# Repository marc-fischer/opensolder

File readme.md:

# Marcs OpenSolder
Fully open source JBC T245-compatible soldering station and tool holder, forked from [howie-j's opensolder](https://github.com/howie-j/opensolder)

## Introduction
When looking to buy a genuine JBC station to replace my dated ERSA icon Pico I've came across howie-j's opensolder. That was already pretty close to my requirements, so i forked this repo. 

## Goals:
- _T12 clone_ form factor that does not take up valuable bench space
- Optional USB connection to PID tune and compensate offsets
- Add a tag-connect debug connector 
- Add a I2C to the breakout to be able to extend functionality afterwards (ie. desolder station)
- JBC T245 tip compatibility, with similar performance to the original station
- QoL features that the CDB station have, like auto standby, tip remover, holder, tip cleaner etc.
- Simple design using cheap off-the-shelf parts
- A compact handpiece stand with these features:
	- Detection when the handpiece is in the tool holder (auto standby)
	- Detection when you're about to swap tips (cut power)
	- Integrated tip remover, tip storage, tip cleaner and a soldering wire spool holder
	- Simple to build

## Design Specifications
- 24V toroidal transformer
- Zero Crossing AC switching
- OLED display and rotary encoder for adjusting temperature
- Compact and low profile design
- Super fast heatup time (~4s)
- Hardware should be mostly 3D printable, and easy to build using regular tools

## Station
  
The station is built in a Hammond enclosure, with a center mounted transformer. The PCB is mounted to the custom front panel, and all 230VAC connections is in the rear of the chassis.
There is two connectors on the rear panel, one for connecting to the stand, and an optional ST-link connector for firmware upgrades.

## Stand
  
The stand is made of 3D-printed parts, a genuine JBC tool holder, a tip remover made from aluminium angle and some fasteners. Most parts can be made from aluminium sheet if that is preferred.

## Schematic
This is the internal connections of the JBC C245 cartridge:  

[__The schematic__](https://github.com/howie-j/OpenSolder/raw/main/hardware/schematic.pdf) is divided into three sheets: AC, Analog and MCU.

### AC
The 24VAC input is fused, then connected directly to the tip center pin (5). Switching is done with two N-channel mosfets, driven by a Si8751 isolated gate driver.

Zero cross detection is done with an AC optocoupler, and the current is limited by three 10k resistors (to reduce BOM items). This solution triggers the ZeroCross about 90uS prematurely, and that is compensated for in firmware.

The MCU and thermocouple frontend must be electrically isolated, and a 24V to 5V DCDC PSU module solves that problem. The DCDC-supply is preregulated with a 24V linear regulator, and post-regulated to 3.3V with a LDO. This power supply chain is in need of some simplification, but the components are few and cheap, and it works great for now.

### Analog
The thermocouple signal is amplified with a MAX4238 chopper opamp, with a fairly arbitrary amplification of 221, since temperature calibration is done in firmware anyway. No negative supply rail means the thermocouple can't sense lower temperatures than room temp, but that's not needed for a soldering station.

Long handpiece wires means lots of crosstalk, so a pair of diodes clamps the thermocouple input at Vf. The MCU pin _TIP_CLAMP_ is driven low when power is applied to the handpiece, to clamp noise on the opamp input. When its time to measure tip temperature, the pin is set to input, and a delay waits for the RC filter to stabilize.

To sense if there is a tip cartridge in the handpiece, _TIP_CHECK_ is driven high. The low impedance of the thermocouple + heater (a few Ω's) will create a very low voltage drop. If the tip is removed, the Vf of the input protection diode will drive _THERMOCOUPLE_ADC_ close to 3.3V.

### MCU
A STM32F072 is used since I have a few of them in stock, but almost any STM32 could be adapted to work. To sense PCB temperature (and for cold junction compensation), an I2C temp sensor is added. The MCU might have an internal temperature sensor, but  have not looked into that yet.

The rotary encoder and handpiece stand inputs are filtered using plain RC filters. This, combined with the input hysteresis, removes most input noise. The TIM encoder inputs also have additional filtering and FSM redundancy.

## PCB
[___Check out this interactive BOM___](http://htmlpreview.github.io/?https://github.com/howie-j/OpenSolder/blob/main/hardware/bom/interactive_bom.html)

The PCB is quite low density, uses 0603 SMD components and is fully hand solderable with a microscope. Connections to the rear connectors (stand and I2C-2 breakout) is done via a 6-pin IDC connector, so no crimping of tiny connector pins are necessary. The PCB is mounted to the front panel via the rotary encoder and the handpiece connector.

## Firmware
The firmware is simple and functional, and uses a modified hysteresis temperature controller that is very fast but has some initial overshoot. Currently all default values are set in _opensolder.h_, and are reset when the station is powered off.

### TODO
Nothing is currently missing for regular functionality. However some features would be cool to have:

- More accurate temp control (PID or other controller)
- User changeable default values
- Menu for changing default values
- Better looking UI

## Links and Sources
[The unisolder project](https://github.com/sparkybg/UniSolder-5.2) 
[Marco Reps](https://youtu.be/GYIiOkr6x9o) 
[foldvarid93's JBC Soldering Station](https://github.com/foldvarid93/JBC_SolderingStation) 
[johnmx's eevblog thread](https://eevblog.com/forum/testgear/jbc-soldering-station-cd-2bc-complete-schematic-analysis/) 
[howie-j's opensolder](https://github.com/howie-j/opensolder)

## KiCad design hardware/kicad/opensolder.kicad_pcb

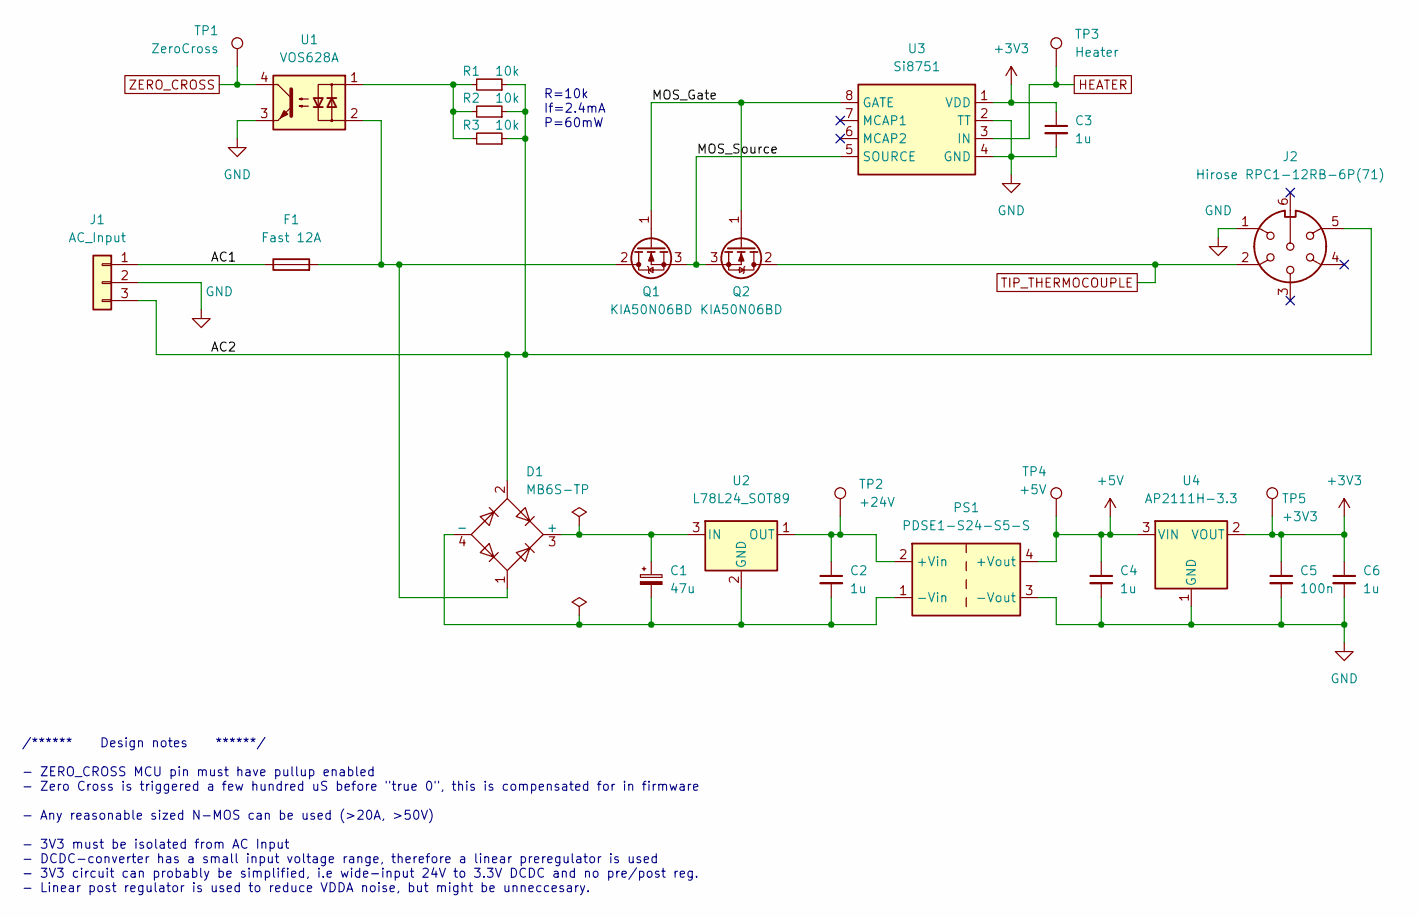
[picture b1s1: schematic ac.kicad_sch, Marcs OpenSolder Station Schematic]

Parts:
C1: 47u; CP_Radial_D8.0mm_P3.50mm
C2, C3, C4, C6: 1u; C_1210_3225Metric
C5: 100n; C_0805_2012Metric
D1: MB6S-TP; TO-269AA
F1: Fast 12A; Fuseholder_Cylinder-5x20mm_Schurter_0031_8201_Horizontal_Op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
J1: AC_Input; PhoenixContact_MSTBVA_2,5_3-G_1x03_P5.00mm_Vertical
J2: Hirose RPC1-12RB-6P(71); Hirose_RPC1
PS1: PDSE1-S24-S5-S; PDSE1_DCDC
Q1, Q2: KIA50N06BD; TO-252-2
R1, R2, R3: 10k; R_0603_1608Metric
TP1: ZeroCross; TestPoint_Pad_D1.0mm
TP2: +24V; TestPoint_Pad_D1.0mm
TP3: Heater; TestPoint_Pad_D1.0mm
TP4: +5V; TestPoint_Pad_D1.0mm
TP5: +3V3; TestPoint_Pad_D1.0mm
U1: VOS628A; SOP-4_4.4x2.6mm_P1.27mm
U2: L78L24_SOT89; SOT-89-3
U3: Si8751; SOIC-8_3.9x4.9mm_P1.27mm
U4: AP2111H-3.3; SOT-223

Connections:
+3V3: C3.1, C5.1, C6.1, TP5.1, U3.1 (VDD), U4.2 (VOUT); also elsewhere on the board
+5V: C4.1, PS1.4 (+Vout), TP4.1, U4.3 (VIN); also elsewhere on the board
/AC/AC1: F1.1, J1.1
/AC/AC2: D1.2, J1.3, J2.5, R1.1, R2.1, R3.1
/AC/MOS_Gate: Q1.1 (G), Q2.1 (G), U3.8 (GATE)
/AC/MOS_Source: Q1.3 (S), Q2.3 (S), U3.5 (SOURCE)
GND: C3.2, C4.2, C5.2, C6.2, J1.2, J2.1, PS1.3 (-Vout), U1.3, U3.2 (TT), U3.4 (GND), U4.1 (GND); also elsewhere on the board
HEATER: TP3.1, U3.3 (IN); also elsewhere on the board
unnamed: C1.1, D1.3 (+), U2.3 (IN)
unnamed: C1.2, C2.2, D1.4 (-), PS1.1 (-Vin), U2.2 (GND)
unnamed: C2.1, PS1.2 (+Vin), TP2.1, U2.1 (OUT)
unnamed: D1.1, F1.2, Q1.2 (D), U1.2
unnamed: R1.2, R2.2, R3.2, U1.1
TIP_THERMOCOUPLE: J2.2, Q2.2 (D); also elsewhere on the board
ZERO_CROSS: TP1.1, U1.4; also elsewhere on the board

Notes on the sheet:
R=10k If=2.4mA P=60mW
/****** Design notes ******/ - ZERO_CROSS MCU pin must have pullup enabled - Zero Cross is triggered a few hundred uS before "true 0", this is compensated for in firmware - Any reasonable sized N-MOS can be used (>20A, >50V) - 3V3 must be isolated from AC Input - DCDC-converter has a small input vo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

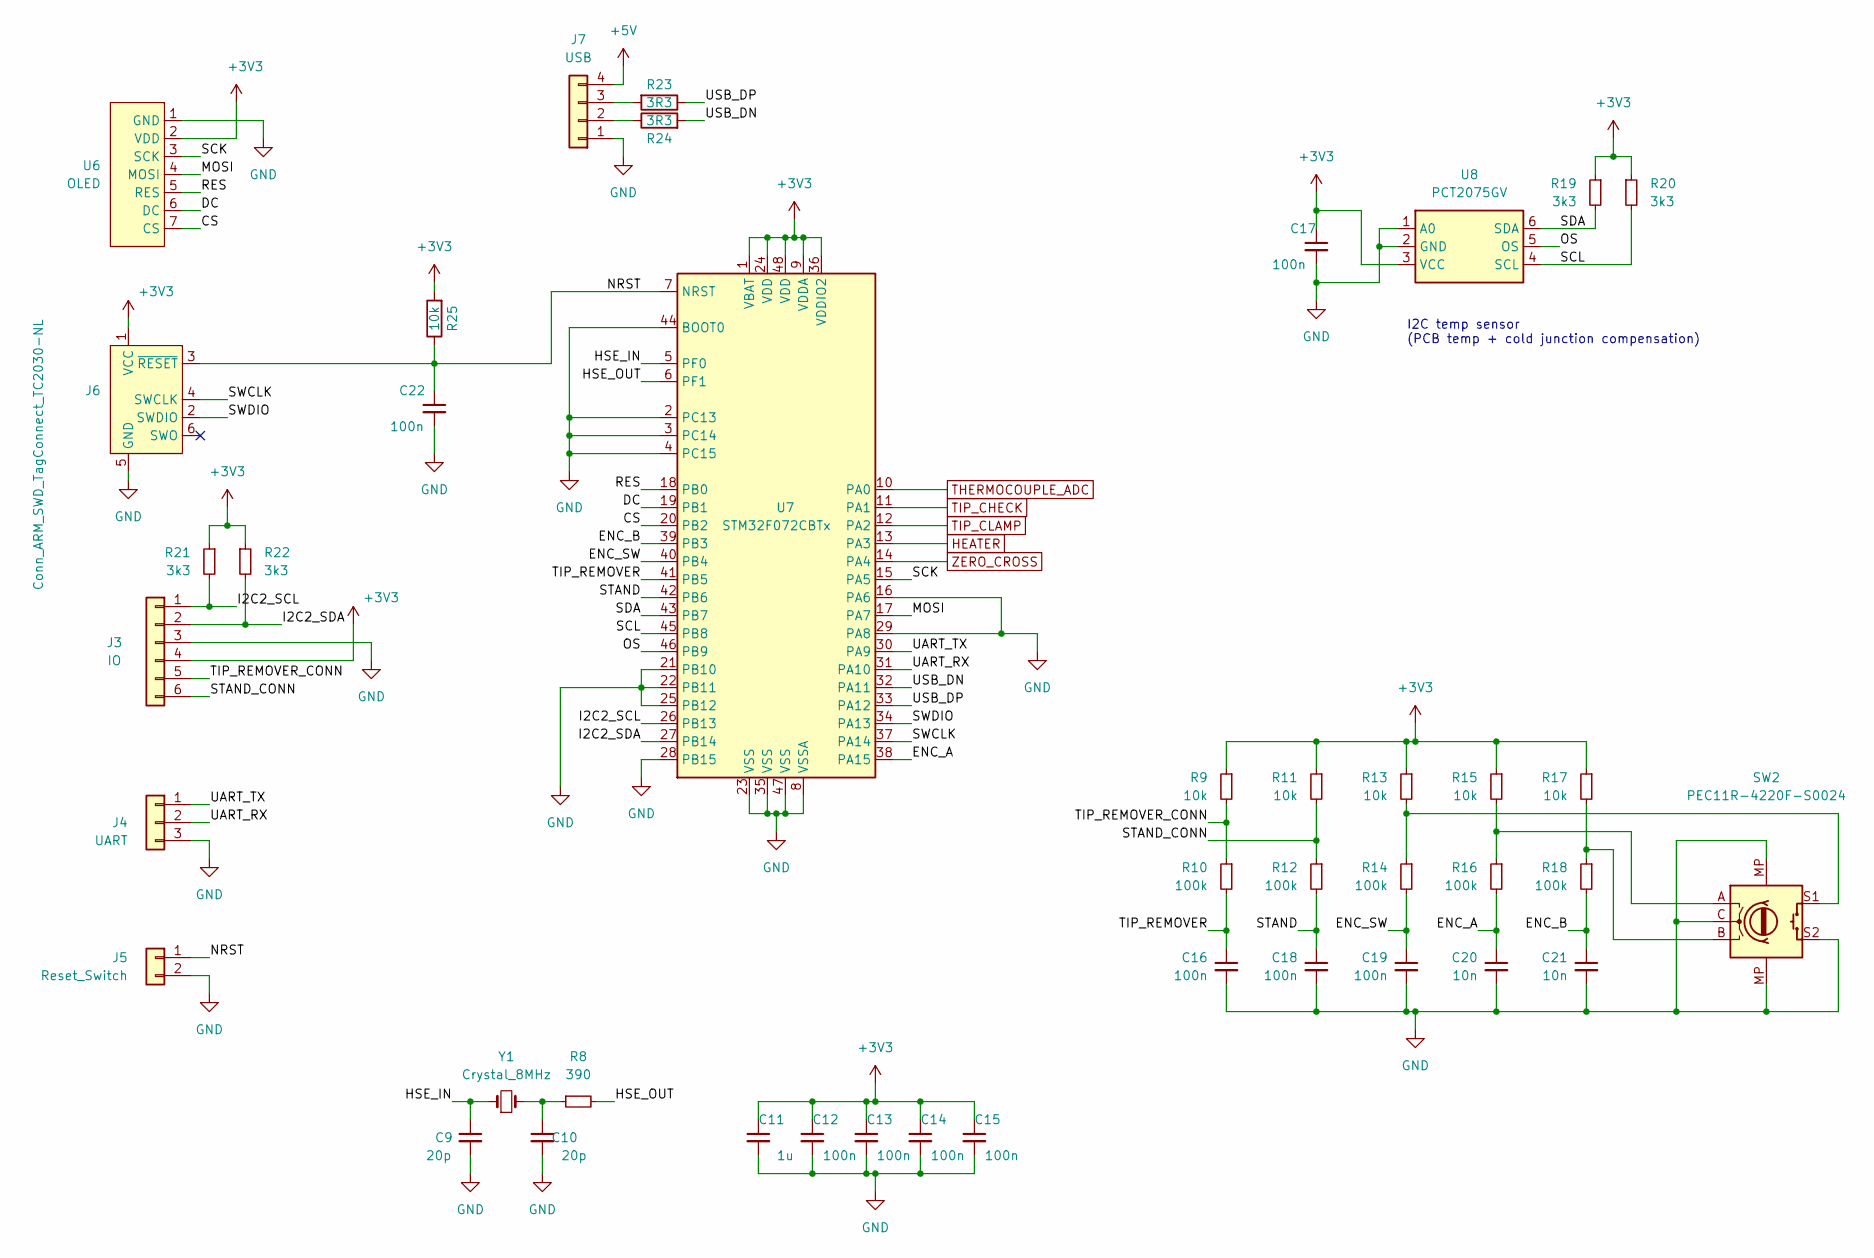
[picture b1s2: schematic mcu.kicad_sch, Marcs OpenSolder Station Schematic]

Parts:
C9, C10: 20p; C_0603_1608Metric
C11: 1u; C_1210_3225Metric
C12, C13, C14, C15: 100n; C_0805_2012Metric
C16, C17, C18, C19, C22: 100n; C_0603_1608Metric
C20, C21: 10n; C_0603_1608Metric
J3: IO; PinHeader_2x03_P2.54mm_Vertical
J4: UART; PinSocket_1x03_P2.54mm_Vertical
J5: Reset_Switch; PinSocket_1x02_P2.54mm_Vertical
J6: Conn_ARM_SWD_TagConnect_TC2030-NL; Tag-Connect_TC2030-IDC-NL_2x03_P1.27mm_Vertical
J7: USB; PinSocket_1x04_P2.54mm_Vertical
R8: 390; R_0603_1608Metric
R9, R11, R13, R15, R17, R25: 10k; R_0603_1608Metric
R10, R12, R14, R16, R18: 100k; R_0603_1608Metric
R19, R20, R21, R22: 3k3; R_0603_1608Metric
R23, R24: 3R3; R_0603_1608Metric
SW2: PEC11R-4220F-S0024; RotaryEncoder_PEC11R_PEC12R
U6: OLED; OLED_SSD1306_SPI_1.54
U7: STM32F072CBTx; LQFP-48_7x7mm_P0.5mm
U8: PCT2075GV; TSOP-6_1.65x3.05mm_P0.95mm
Y1: Crystal_8MHz; Crystal_SMD_HC49-SD

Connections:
+3V3: C11.1, C12.1, C13.1, C14.1, C15.1, C17.1, J3.4, J6.1 (VCC), R9.1, R11.1, R13.1, R15.1, R17.1, R19.1, R20.1, R21.1, R22.1, R25.2, U6.2 (VDD), U7.1 (VBAT), U7.9 (VDDA), U7.24 (VDD), U7.36 (VDDIO2), U7.48 (VDD), U8.3 (VCC); also elsewhere on the board
+5V: J7.4; also elsewhere on the board
/MCU/CS: U6.7 (CS), U7.20 (PB2)
/MCU/DC: U6.6 (DC), U7.19 (PB1)
/MCU/ENC_A: C20.1, R16.2, U7.38 (PA15)
/MCU/ENC_B: C21.1, R18.2, U7.39 (PB3)
/MCU/ENC_SW: C19.1, R14.2, U7.40 (PB4)
/MCU/HSE_IN: C9.1, U7.5 (PF0), Y1.1
/MCU/HSE_OUT: R8.2, U7.6 (PF1)
/MCU/I2C2_SCL: J3.1, R21.2, U7.26 (PB13)
/MCU/I2C2_SDA: J3.2, R22.2, U7.27 (PB14)
/MCU/MOSI: U6.4 (MOSI), U7.17 (PA7)
/MCU/NRST: C22.1, J5.1, J6.3 (~RESET), R25.1, U7.7 (NRST)
/MCU/OS: U7.46 (PB9), U8.5 (OS)
/MCU/RES: U6.5 (RES), U7.18 (PB0)
/MCU/SCK: U6.3 (SCK), U7.15 (PA5)
/MCU/SCL: R20.2, U7.45 (PB8), U8.4 (SCL)
/MCU/SDA: R19.2, U7.43 (PB7), U8.6 (SDA)
/MCU/STAND: C18.1, R12.2, U7.42 (PB6)
/MCU/STAND_CONN: J3.6, R11.2, R12.1
/MCU/SWCLK: J6.4 (SWCLK), U7.37 (PA14)
/MCU/SWDIO: J6.2 (SWDIO), U7.34 (PA13)
/MCU/TIP_REMOVER: C16.1, R10.2, U7.41 (PB5)
/MCU/TIP_REMOVER_CONN: J3.5, R9.2, R10.1
/MCU/UART_RX: J4.2, U7.31 (PA10)
/MCU/UART_TX: J4.1, U7.30 (PA9)
/MCU/USB_DN: R24.2, U7.32 (PA11)
/MCU/USB_DP: R23.1, U7.33 (PA12)
GND: C9.2, C10.2, C11.2, C12.2, C13.2, C14.2, C15.2, C16.2, C17.2, C18.2, C19.2, C20.2, C21.2, C22.2, J3.3, J4.3, J5.2, J6.5 (GND), J7.1, SW2.C, SW2.MP, SW2.S2, U6.1 (GND), U7.2 (PC13), U7.3 (PC14), U7.4 (PC15), U7.8 (VSSA), U7.16 (PA6), U7.21 (PB10), U7.22 (PB11), U7.23 (VSS), U7.25 (PB12), U7.28 (PB15), U7.29 (PA8), U7.35 (VSS), U7.44 (BOOT0), U7.47 (VSS), U8.1 (A0), U8.2 (GND); also elsewhere on the board
HEATER: U7.13 (PA3); also elsewhere on the board
unnamed: C10.1, R8.1, Y1.2
unnamed: J7.2, R24.1
unnamed: J7.3, R23.2
unnamed: R13.2, R14.1, SW2.S1
unnamed: R15.2, R16.1, SW2.A
unnamed: R17.2, R18.1, SW2.B
THERMOCOUPLE_ADC: U7.10 (PA0); also elsewhere on the board
TIP_CHECK: U7.11 (PA1); also elsewhere on the board
TIP_CLAMP: U7.12 (PA2); also elsewhere on the board
ZERO_CROSS: U7.14 (PA4); also elsewhere on the board

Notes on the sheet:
I2C temp sensor (PCB temp + cold junction compensation)

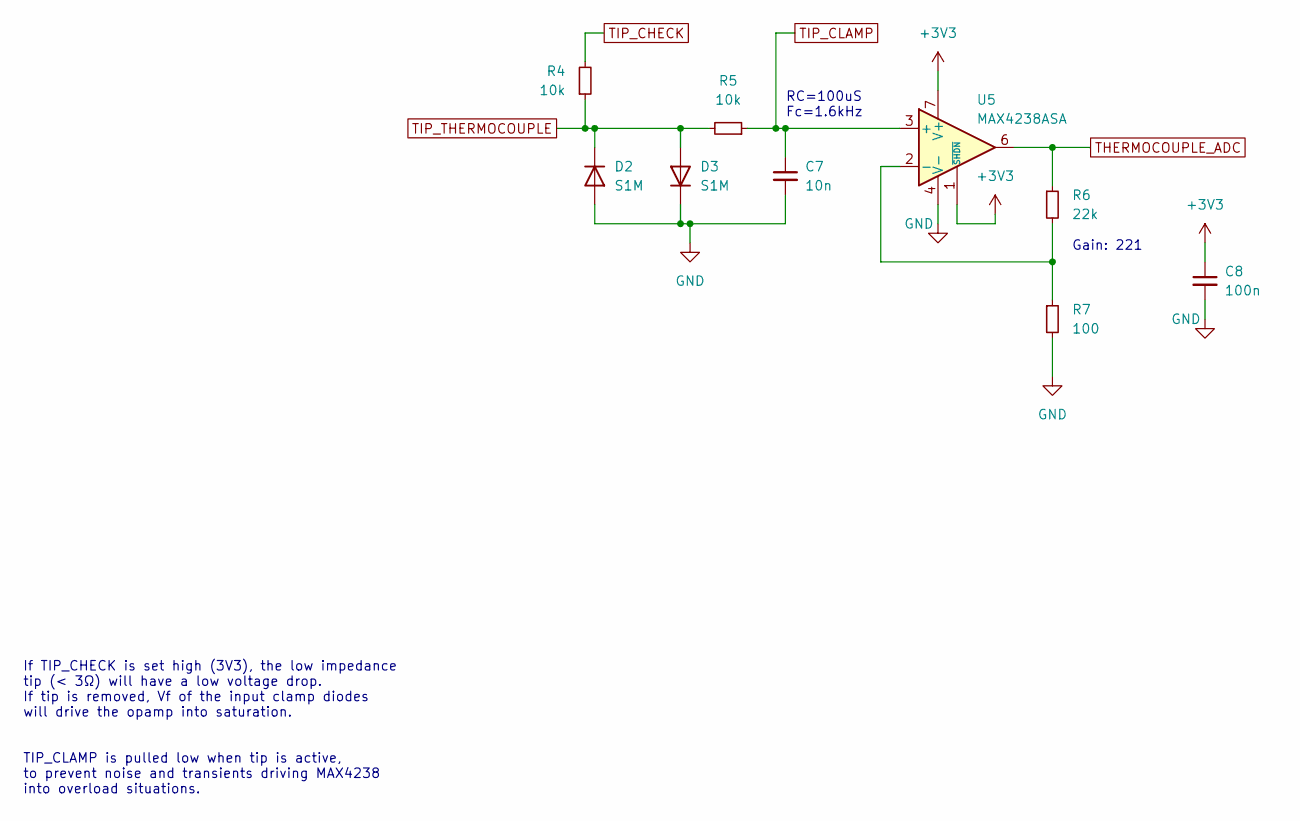
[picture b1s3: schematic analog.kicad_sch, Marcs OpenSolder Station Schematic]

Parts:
C7: 10n; C_0603_1608Metric
C8: 100n; C_0603_1608Metric
D2, D3: S1M; D_SMA
R4, R5: 10k; R_0603_1608Metric
R6: 22k; R_0603_1608Metric
R7: 100; R_0603_1608Metric
U5: MAX4238ASA; SOIC-8_3.9x4.9mm_P1.27mm

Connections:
+3V3: C8.1, U5.1 (~SHDN), U5.7 (V+); also elsewhere on the board
GND: C7.2, C8.2, D2.2 (A), D3.1 (K), R7.2, U5.4 (V-); also elsewhere on the board
unnamed: R6.2, R7.1, U5.2 (-)
THERMOCOUPLE_ADC: R6.1, U5.6; also elsewhere on the board
TIP_CHECK: R4.2; also elsewhere on the board
TIP_CLAMP: C7.1, R5.1, U5.3 (+); also elsewhere on the board
TIP_THERMOCOUPLE: D2.1 (K), D3.2 (A), R4.1, R5.2; also elsewhere on the board

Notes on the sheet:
Gain: 221
RC=100uS Fc=1.6kHz
If TIP_CHECK is set high (3V3), the low impedance tip (< 3Ω) will have a low voltage drop. If tip is removed, Vf of the input clamp diodes will drive the opamp into saturation. TIP_CLAMP is pulled low when tip is active, to prevent noise and transients driving MAX4238 into overload situations.

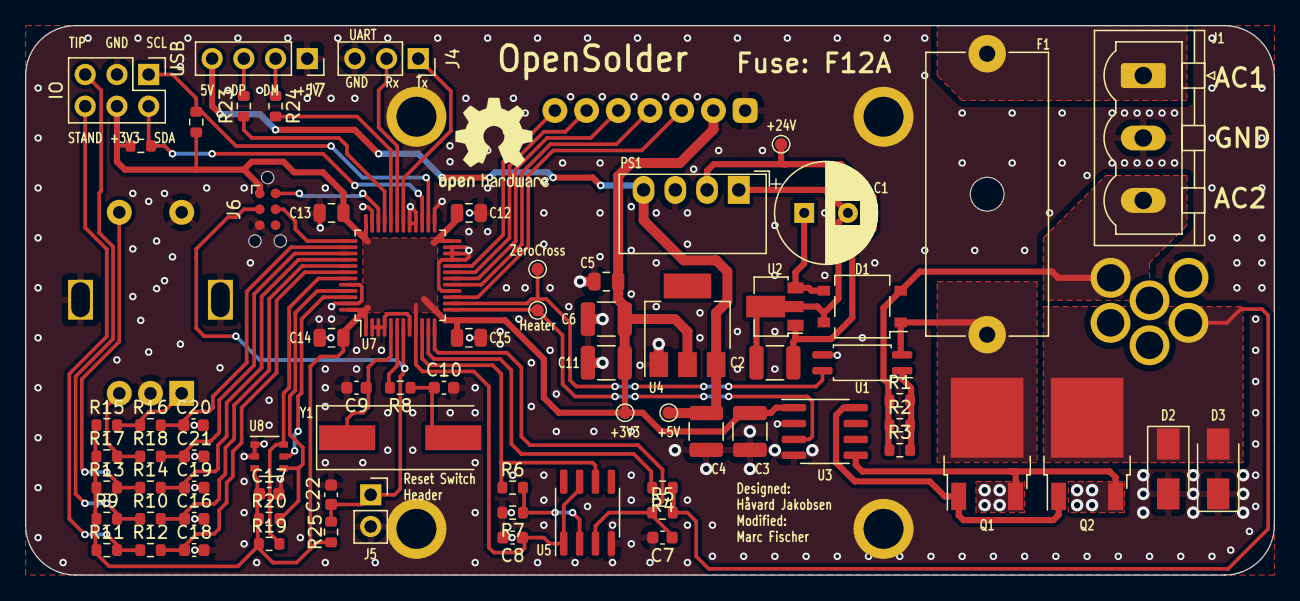
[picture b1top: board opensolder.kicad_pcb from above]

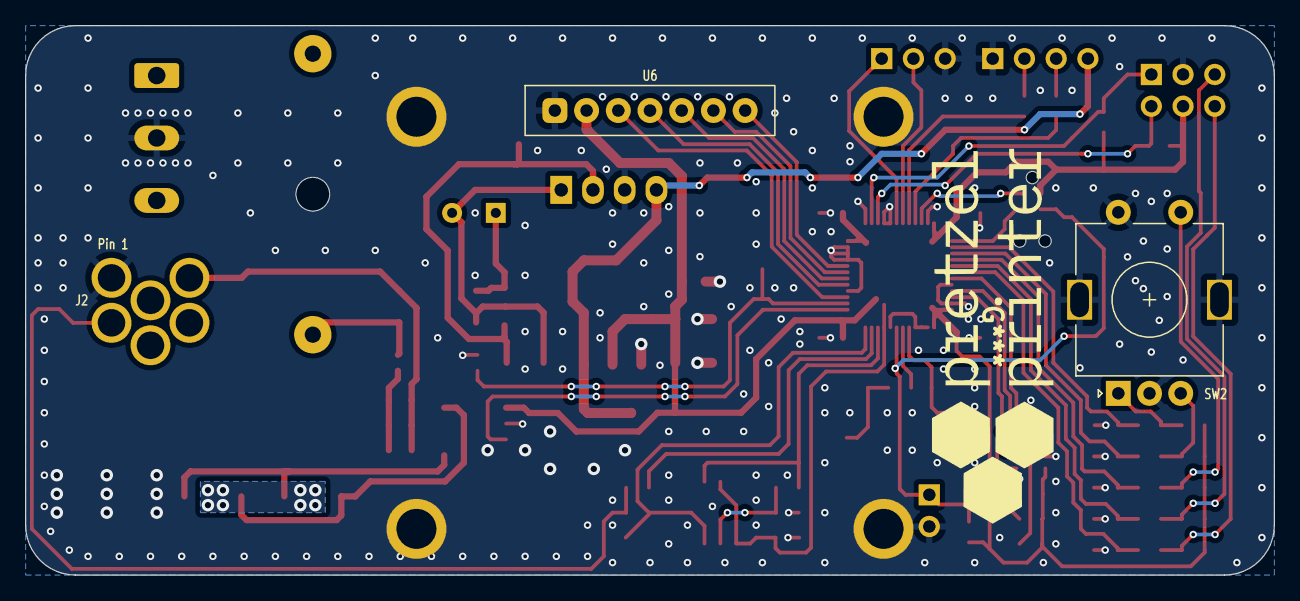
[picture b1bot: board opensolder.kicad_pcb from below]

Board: 2 copper layers, 100.0 x 44.0 mm, 76 parts (3 on the bottom side), 51 nets.

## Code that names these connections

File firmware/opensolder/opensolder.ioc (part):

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Mcu.Name=STM32F072C(8-B)Tx
Mcu.Package=LQFP48
Mcu.UserName=STM32F072CBTx
PA0.GPIOParameters=GPIO_Label
PA0.GPIO_Label=THERMOCOUPLE_ADC
PA0.Mode=IN0
PA0.Signal=ADC_IN0
PA1.GPIOParameters=GPIO_Label
PA1.GPIO_Label=TIP_CHECK
PA1.Signal=GPIO_Input
PA10.Mode=Asynchronous
PA10.Signal=USART1_RX
PA11.Mode=Device
PA11.Signal=USB_DM
PA12.Mode=Device
PA12.Signal=USB_DP
PA13.Mode=Serial_Wire
PA13.Signal=SYS_SWDIO
PA14.Mode=Serial_Wire
PA14.Signal=SYS_SWCLK
PA15.GPIOParameters=GPIO_Label
PA15.GPIO_Label=ENC_A
PA15.Signal=S_TIM2_CH1_ETR
PA2.GPIOParameters=GPIO_Label
PA2.GPIO_Label=TIP_CLAMP
PA2.Signal=GPIO_Input
PA3.GPIOParameters=GPIO_Label
PA3.GPIO_Label=HEATER
PA3.Signal=GPIO_Output
PA4.GPIOParameters=GPIO_PuPd,GPIO_Label
PA4.GPIO_Label=ZERO_CROSS
PA4.GPIO_PuPd=GPIO_PULLUP
PA4.Signal=GPXTI4
PA5.Mode=Simplex_Bidirectional_Master
PA5.Signal=SPI1_SCK
PA7.Mode=Simplex_Bidirectional_Master
PA7.Signal=SPI1_MOSI
PA9.Mode=Asynchronous
PA9.Signal=USART1_TX
PB0.GPIOParameters=GPIO_Label
PB0.GPIO_Label=RES
PB0.Signal=GPIO_Output
PB1.GPIOParameters=GPIO_Label
PB1.GPIO_Label=DC
PB1.Signal=GPIO_Output
PB13.Mode=I2C
PB13.Signal=I2C2_SCL
PB14.Mode=I2C
PB14.Signal=I2C2_SDA
PB2.GPIOParameters=GPIO_Label
PB2.GPIO_Label=CS
PB2.Signal=GPIO_Output
PB3.GPIOParameters=GPIO_Label
PB3.GPIO_Label=ENC_B
PB3.Signal=S_TIM2_CH2
PB4.GPIOParameters=GPIO_Label
PB4.GPIO_Label=ENC_SW
PB4.Signal=GPIO_Input
PB5.GPIOParameters=GPIO_PuPd,GPIO_Label
PB5.GPIO_Label=TIP_REMOVER
PB5.GPIO_PuPd=GPIO_NOPULL
PB5.Signal=GPIO_Input
PB6.GPIOParameters=GPIO_PuPd,GPIO_Label
PB6.GPIO_Label=STAND
PB6.GPIO_PuPd=GPIO_NOPULL
PB6.Signal=GPIO_Input
PB7.Mode=I2C
PB7.Signal=I2C1_SDA
PB8.Mode=I2C
PB8.Signal=I2C1_SCL
PB9.GPIOParameters=GPIO_PuPd,GPIO_Label
PB9.GPIO_Label=OS
PB9.GPIO_PuPd=GPIO_PULLUP
PB9.Signal=GPIO_Input
PF0-OSC_IN.Mode=HSE-External-Oscillator
PF0-OSC_IN.Signal=RCC_OSC_IN
PF1-OSC_OUT.Mode=HSE-External-Oscillator
PF1-OSC_OUT.Signal=RCC_OSC_OUT
RCC.SYSCLKFreq_VALUE=48000000
RCC.SYSCLKSource=RCC_SYSCLKSOURCE_PLLCLK
board=custom

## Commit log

2023-12-28 removed output folder from git (to be posted as release)
2023-12-28 removed debug output and settings from firmware (user specific)
2023-12-28 removed opensolder releases
2023-12-28 ignore kicad-backups folder
2023-12-28 [HW] Add: - Tag Connect Debug connector - USB & I2C breakout - GND pin to UART breakout
2023-12-28 update readme with project information
2023-12-28 [FW]: Move SSD1306 code from core to Drivers
2023-12-28 rename xxx placeholder to zzz to hide todo in STM32cubeide
2023-12-28 add Datasheets
2023-12-28 [FW]: split temperature handlers for pcb temperature and tip temperature in different files move pcb temperature to driver folder
2023-12-28 [FW]: - Update STM32f0xx HAL - Add USB, timer14, I2C2, UART
2023-12-28 [FW]: - Abstract Tip check to a driver
2023-12-28 [FW]: - Move Tip Clamp functionality to a driver
2023-12-28 [FW]: - Move Heater Function to a driver, add low-level protection to the driver
2023-12-28 [FW]: - Split "temperature.c" to different files: -- tip_thermocouple - handles all measurement related tasks -- timers - handles interrupts and timers -- tip_heater - handles all heating related tas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
2023-12-28 [FW]: - Auto-Format the Code
2023-12-28 [FW]: - Update Readme
2023-12-28 Remove Backup Folders from git
2024-01-04 [FW]:
    Move buttons to HID class, add additional timer for HID, move main state machine to opensolder_main loop
2024-01-04 [FW]:
    Implement better naming schemes for functions

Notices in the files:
hardware/kicad/ac.kicad_sch:
Licence: GPL-3.0
